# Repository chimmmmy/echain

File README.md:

# echain

a smart keychain with an e ink display, powered by seed studio nrf52840

# objectives

1. show a smart pet on the front that can be interacted with via the two buttons on the back of the device

2. show music and notifications from phone by using bluetooth

3. off screen should show a customizable image that can be sent to the device over bluetooth

4. battery should last at LEAST a month

5. utilize the nrf52480's deep sleep function to increase battery life

6. prototypes out of plastic, final out of cnc aluminum

# current capabilities (untested)

* show a basic landscape display

* connect to an android phone via bluetooth

* change off screen via bluetooth

* show music currently being played via bluetooth

* interactable via 2 buttons

* able to enter deep sleep and exit deep sleep

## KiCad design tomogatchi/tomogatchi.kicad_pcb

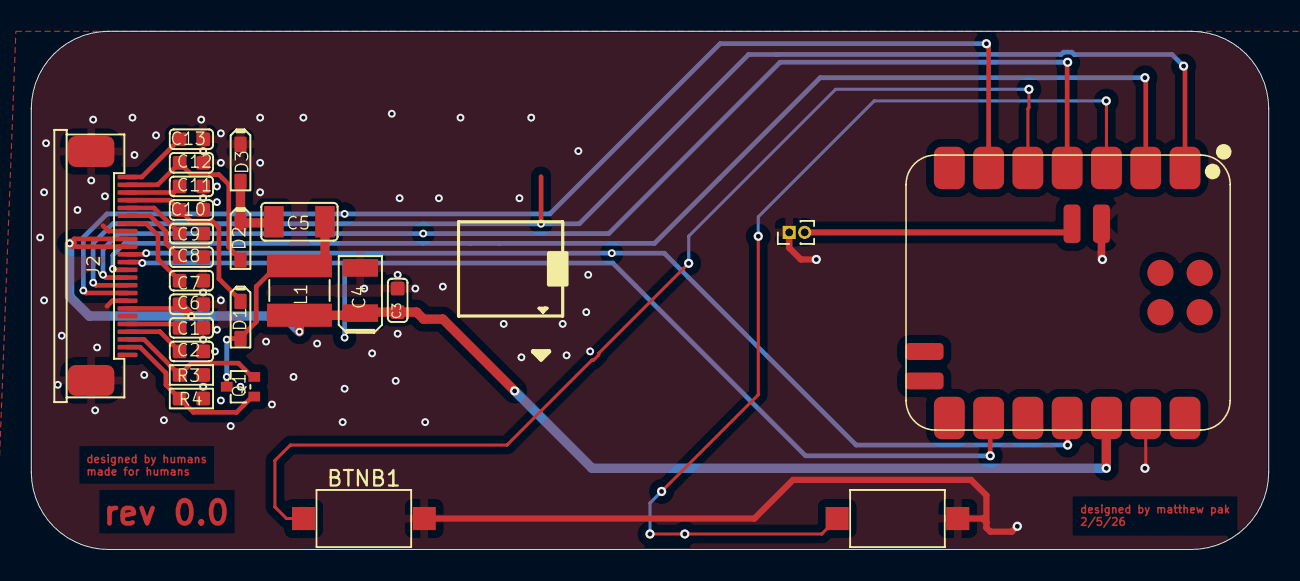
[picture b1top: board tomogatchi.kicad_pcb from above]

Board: 2 copper layers, 80.0 x 33.5 mm, 23 parts (0 on the bottom side), 15 nets.

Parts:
BTNA1: BTN_A; SW_SPST_CK_RS282G05A3
BTNB1: BTN_B; SW_SPST_CK_RS282G05A3
C1, C2, C3, C7, C8, C9, C10, C11, C12, C13: 1uF; C0603
C4: 220uF/6.3V; AVX-B
C5: 4.7uF/50V; C1206
C6: 100nF; C0603
D1, D2, D3: B0540W; SOD-323
J2: Display; FPCB24-SMD-0.5-17.6X5.0X2MM
L1: 10uH; L0420
Q1: Si1304BDL; SOT-323
R3: 0.47R/1%; R0603
R4: 10K; R0603

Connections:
3V3: C3.1, C4.+, C6.2, J2.7, J2.15, J2.16, L1.2
GDR: J2.2, Q1.1, R4.1
GND: BTNA1.2, BTNB1.2, C1.2, C2.2, C3.2, C4.-, C6.1, C7.1, C8.1, C9.1, C10.2, C11.1, C12.1, C13.2, D3.-, J2.8, J2.17, J2.25, J2.26, R3.2, R4.2
unnamed: C2.1, J2.4
unnamed: C5.1, D2.-, D3.+
unnamed: C5.2, D1.+, L1.1, Q1.3
unnamed: C7.2, J2.18
unnamed: C8.2, J2.19
unnamed: C9.2, J2.20
unnamed: C10.1, D1.-, J2.21
unnamed: C11.2, J2.22
unnamed: C12.2, D2.+, J2.23
RESE: J2.3, Q1.2, R3.1
VCOM: C13.1, J2.24
VGH: C1.1, J2.5

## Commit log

2026-03-06 Add files via upload
    added first version of code (stuck in portrait, working on new horizontal driver for the screen)
    probably just going to order a different screen cuz this one is just so finicky
2026-03-06 Update README.md
    added objectives
2026-03-06 cad
    uploaded the original cad files (they dont fit rev 0.1)
2026-03-06 pcb files
2026-03-06 added current state of project
2026-03-11 tragedy
2026-03-11 now with landscape mode
2026-03-11 added ble and music player capability
    untested
2026-03-11 android app v1
2026-03-11 software done!
2026-03-12 added sleep screen functionality
    untested
2026-03-12 made readme easier to read me
2026-03-12 Update README.md
    making things clear
